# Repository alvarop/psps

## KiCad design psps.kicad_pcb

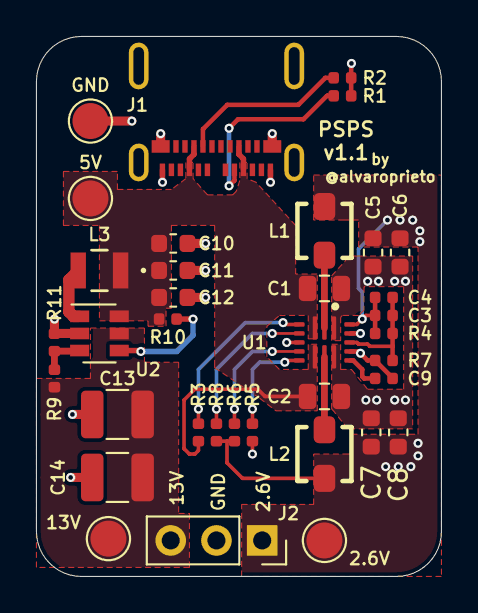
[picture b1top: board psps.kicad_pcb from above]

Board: 2 copper layers, 22.5 x 30.0 mm, 36 parts (0 on the bottom side), 17 nets.

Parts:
2.6V: 2V6; TestPoint_Pad_D2.0mm
5V: 5V; TestPoint_Pad_D2.0mm
13V: 13V; TestPoint_Pad_D2.0mm
C1, C2: 22uF; C_0805_2012Metric
C3, C4: 18pF; C_0402_1005Metric
C5, C6, C7, C8: 22uF; C_0603_1608Metric
C9: 5.6nF; C_0402_1005Metric
C10, C11, C12: 1uF; C_0603_1608Metric
C13, C14: 10uF; C_1210_3225Metric
GND: GND; TestPoint_Pad_D2.0mm
J1: USB_C_Receptacle; MOLEX-1054500101
J2: Conn_01x03; PinSocket_1x03_P2.54mm_Vertical
L1, L2: 470 nH; IHLP1212AEERR47M11
L3: 10uH; MLP2520S100MT0S1
R1, R2: 5.1k; R_0402_1005Metric
R3, R5, R10: 0; R_0402_1005Metric
R4, R6, R8: 402k; R_0402_1005Metric
R7: 120k; R_0402_1005Metric
R9: 1.1M; R_0402_1005Metric
R11: 71.5k; R_0402_1005Metric
U1: TPS62480
U2: TLV61046ADB; SOT-23-6

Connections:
+5V: 5V.1, C1.1, C2.1, C10.1, C11.1, C12.1, J1.A4, J1.A9, J1.B4, J1.B9, L3.1, R3.1, R10.2, U1.3, U1.9, U2.6
/2V6: 2.6V.1, C3.1, C4.1, C5.1, C6.1, C7.1, C8.1, J2.1, L1.2, L2.2, R4.1, R6.2, R8.2, U1.16
/13V: 13V.1, C13.1, C14.1, J2.3, R9.2, U2.5
GND: C1.2, C2.2, C5.2, C6.2, C7.2, C8.2, C9.2, C10.2, C11.2, C12.2, C13.2, C14.2, GND.1, J1.A1, J1.A12, J1.B1, J1.B12, J1.S1, J2.2, R1.1, R2.1, R5.2, R7.2, R11.1, U1.1, U1.6, U1.11, U1.13, U1.15, U2.2
unnamed: C3.2, C4.2, R4.2, R7.1, U1.14
unnamed: C9.1, U1.12
unnamed: J1.A5, R1.2
unnamed: J1.B5, R2.2
unnamed: L1.1, U1.2
unnamed: L2.1, U1.10
unnamed: L3.2, U2.1
unnamed: R3.2, U1.4
unnamed: R5.1, U1.8
unnamed: R6.1, U1.7
unnamed: R8.1, U1.5
unnamed: R10.1, U2.4
unnamed: R9.1, R11.2, U2.3

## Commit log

2019-07-13 First commit of PSPS v1.0
    Released to oshpark
2019-07-21 Released PSPS 1.1 to oshpark

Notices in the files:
parts and their libraries:
Copyright 2016 Accelerated Designs. All rights reserved.
